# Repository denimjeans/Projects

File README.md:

Projekte
========

My self made electronic Projects.
Inclues all Files of the Project (Software and Hardware).

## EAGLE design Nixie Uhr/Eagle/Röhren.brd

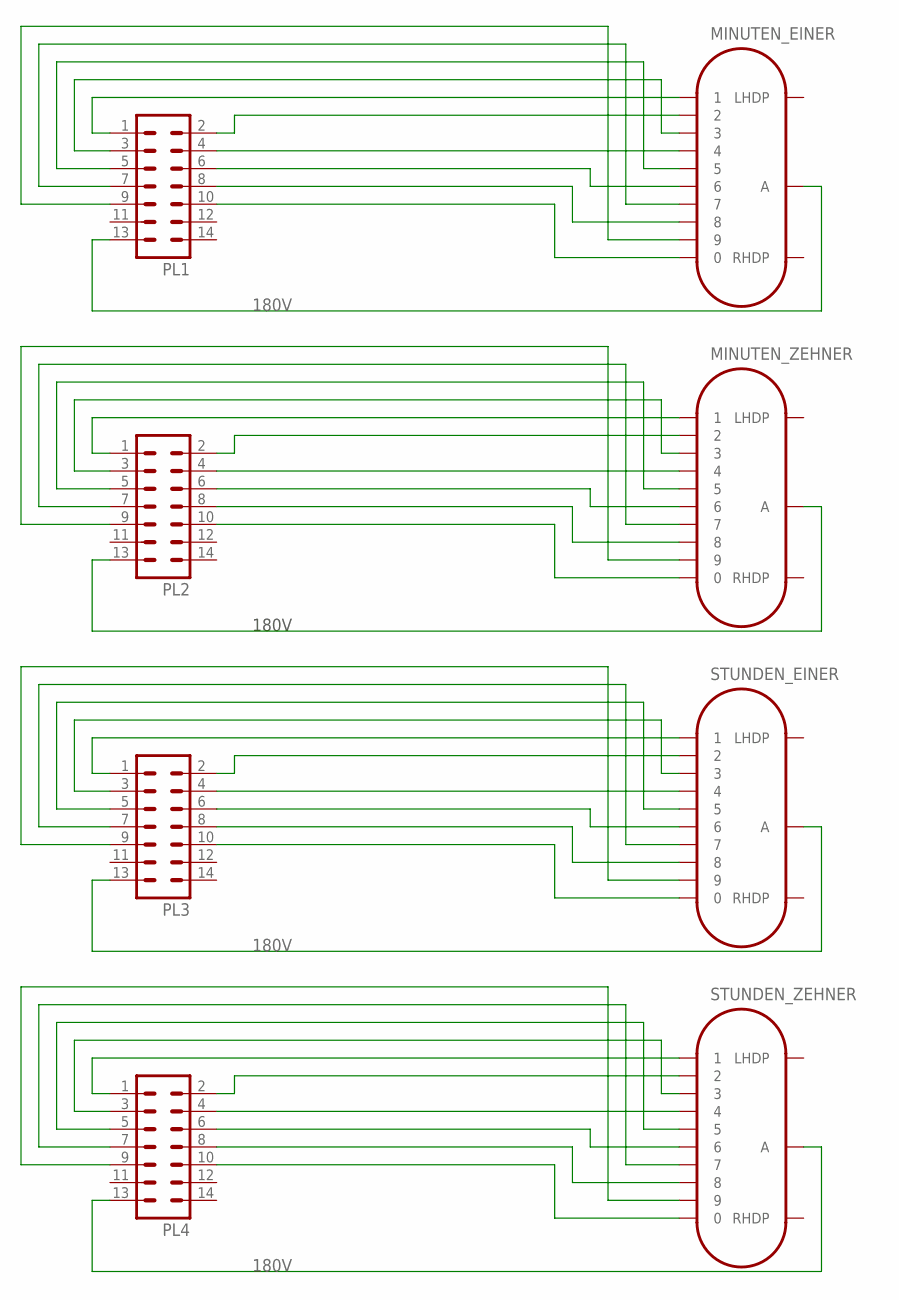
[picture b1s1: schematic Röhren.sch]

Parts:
MINUTEN_EINER: IN-16
MINUTEN_ZEHNER: IN-16
PL1, PL2, PL3, PL4: ML14
STUNDEN_EINER: IN-16
STUNDEN_ZEHNER: IN-16

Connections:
unnamed: MINUTEN_EINER.1, PL1.1
unnamed: MINUTEN_ZEHNER.1, PL2.1
unnamed: PL3.1, STUNDEN_EINER.1
unnamed: PL3.2, STUNDEN_EINER.2
unnamed: MINUTEN_EINER.2, PL1.2
unnamed: MINUTEN_EINER.3, PL1.3
unnamed: MINUTEN_EINER.4, PL1.4
unnamed: MINUTEN_EINER.5, PL1.5
unnamed: MINUTEN_EINER.6, PL1.6
unnamed: MINUTEN_EINER.8, PL1.8
unnamed: MINUTEN_EINER.9, PL1.9
unnamed: MINUTEN_EINER.0, PL1.10
unnamed: MINUTEN_EINER.A, PL1.13
unnamed: MINUTEN_ZEHNER.6, PL2.6
unnamed: MINUTEN_ZEHNER.2, PL2.2
unnamed: MINUTEN_ZEHNER.3, PL2.3
unnamed: MINUTEN_ZEHNER.4, PL2.4
unnamed: MINUTEN_ZEHNER.5, PL2.5
unnamed: MINUTEN_ZEHNER.7, PL2.7
unnamed: MINUTEN_ZEHNER.8, PL2.8
unnamed: MINUTEN_ZEHNER.9, PL2.9
unnamed: MINUTEN_ZEHNER.0, PL2.10
unnamed: MINUTEN_ZEHNER.A, PL2.13
unnamed: PL3.3, STUNDEN_EINER.3
unnamed: PL3.4, STUNDEN_EINER.4
unnamed: PL3.5, STUNDEN_EINER.5
unnamed: PL3.6, STUNDEN_EINER.6
unnamed: PL3.7, STUNDEN_EINER.7
unnamed: PL3.8, STUNDEN_EINER.8
unnamed: PL3.9, STUNDEN_EINER.9
unnamed: PL3.10, STUNDEN_EINER.0
unnamed: PL3.13, STUNDEN_EINER.A
unnamed: PL4.1, STUNDEN_ZEHNER.1
unnamed: PL4.2, STUNDEN_ZEHNER.2
unnamed: PL4.3, STUNDEN_ZEHNER.3
unnamed: PL4.4, STUNDEN_ZEHNER.4
unnamed: PL4.5, STUNDEN_ZEHNER.5
unnamed: PL4.6, STUNDEN_ZEHNER.6
unnamed: PL4.7, STUNDEN_ZEHNER.7
unnamed: PL4.8, STUNDEN_ZEHNER.8
unnamed: PL4.9, STUNDEN_ZEHNER.9
unnamed: PL4.10, STUNDEN_ZEHNER.0
unnamed: PL4.13, STUNDEN_ZEHNER.A
STUNDEN_ZEHNER: MINUTEN_EINER.7, PL1.7

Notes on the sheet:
180V

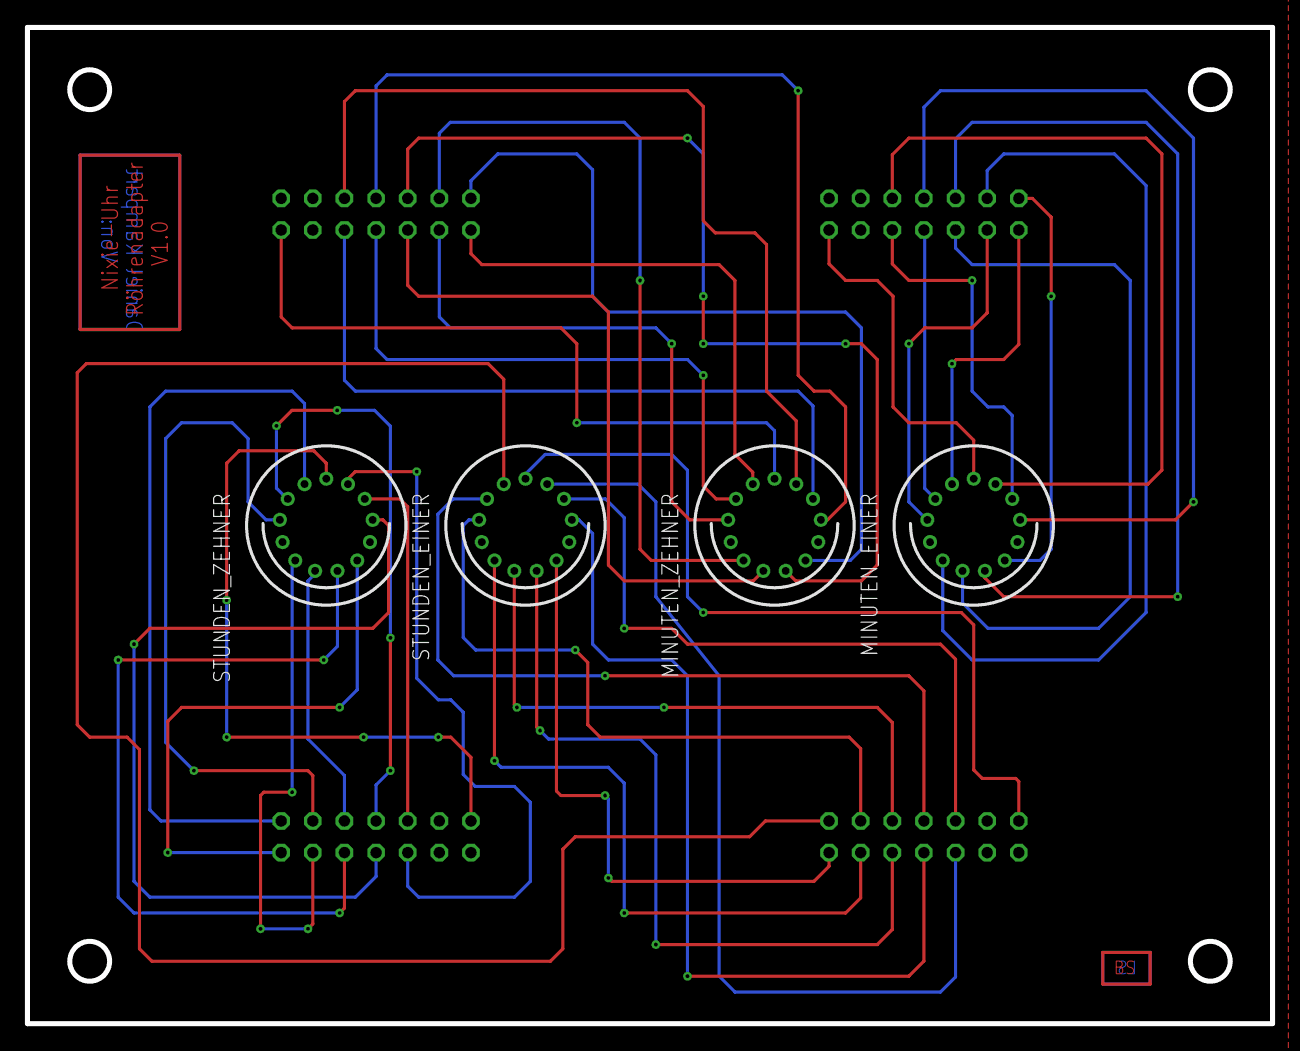
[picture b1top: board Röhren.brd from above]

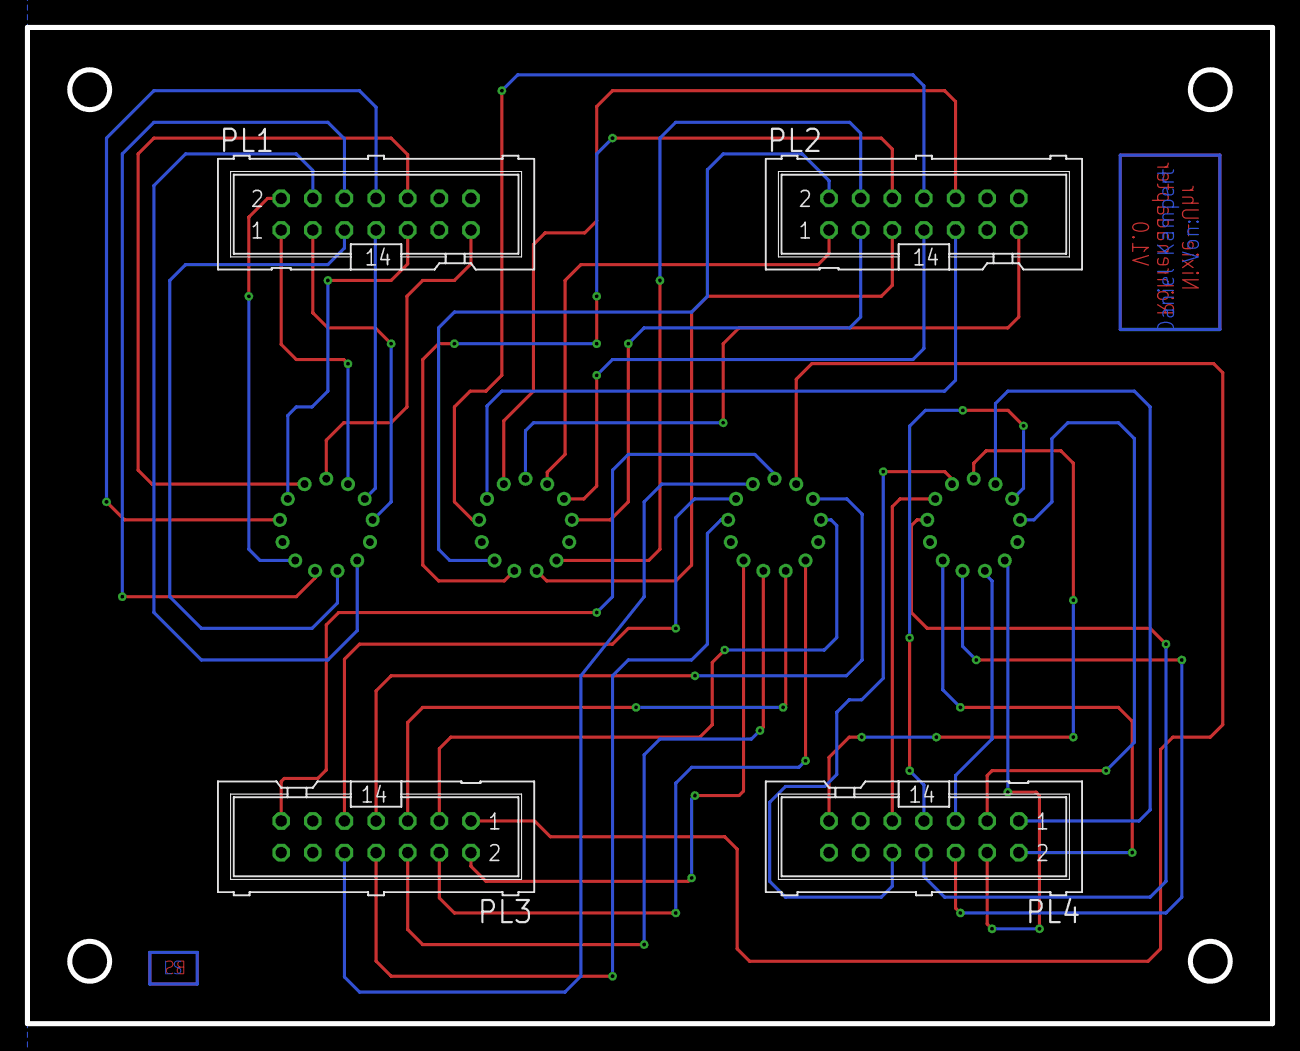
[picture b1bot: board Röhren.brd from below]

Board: 2 copper layers, 100.0 x 80.0 mm, 8 parts (4 on the bottom side), 44 nets.

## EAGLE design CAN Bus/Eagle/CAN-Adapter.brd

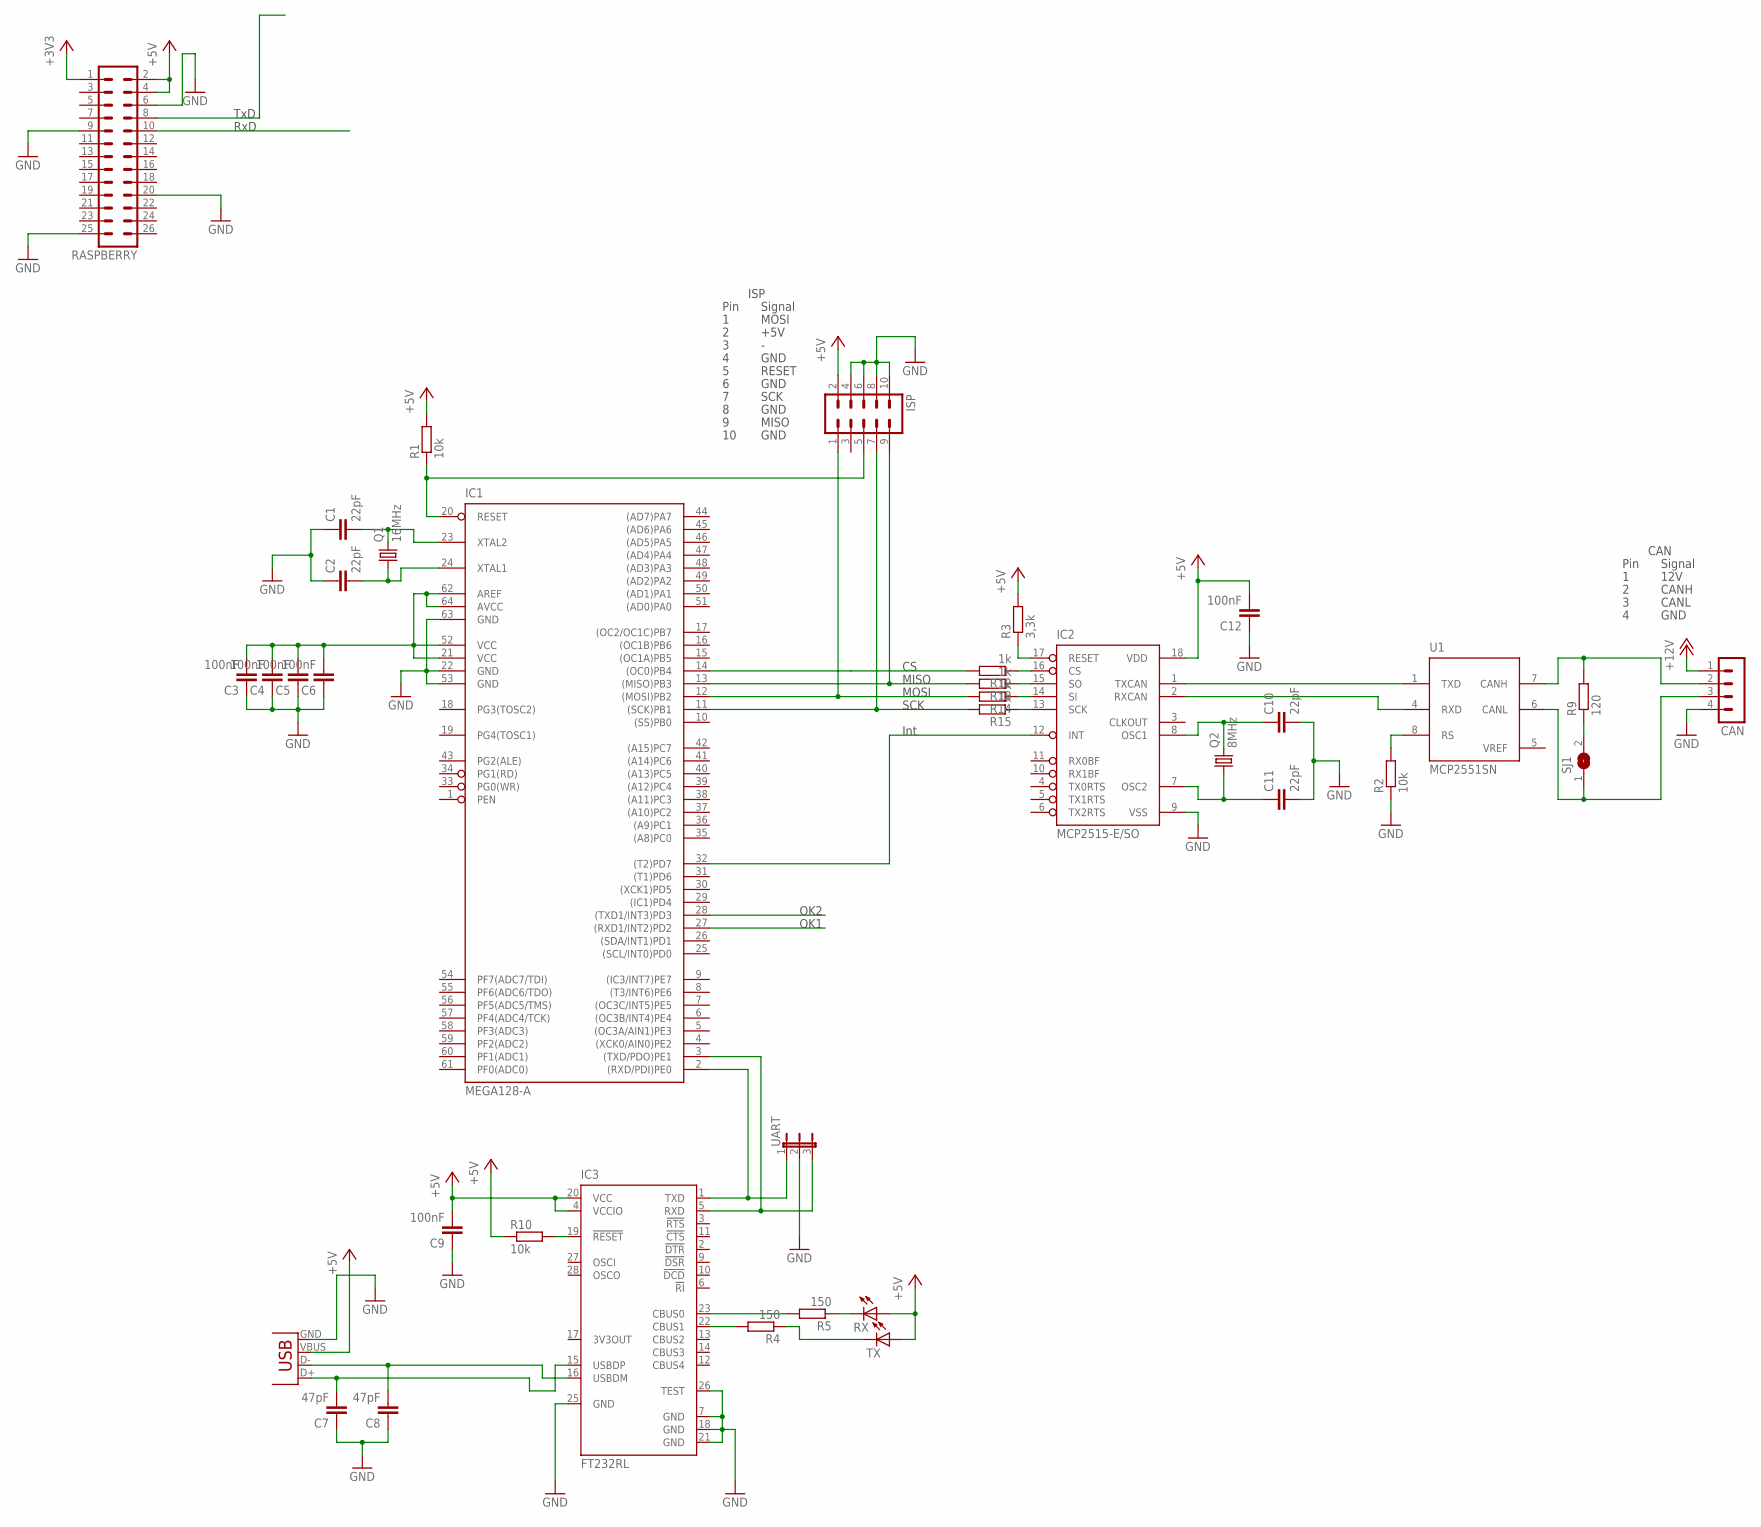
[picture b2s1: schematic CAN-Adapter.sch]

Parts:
C1, C2, C10, C11: 22pF; C0805
C3, C4, C5, C6, C9, C12: 100nF; C0805
C7, C8: 47pF; C0805
CAN: MA04-1
IC1: MEGA128-A; TQFP64
IC2: MCP2515-E/SO; SO18L
IC3: FT232RL; SSOP28
ISP: ML10
Q1: 16MHz; CSM-7X-DU
Q2: 8MHz; HC49UP
R1: 10k; R0805
R2, R10: 10k; M0805
R3: 3,3k; M0805
R4, R5: 150; M0805
R9: 120; M0805
R12, R13, R14, R15: 1k; R0402
RASPBERRY: MA13-2
RX: LEDCHIP-LED0805; CHIP-LED0805
SJ1: SJ
TX: LEDCHIP-LED0805; CHIP-LED0805
U1: MCP2551SN; SO-08
UART: JP2E; JP2
X1: USB-B-H

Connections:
+3V3: RASPBERRY.1
+5V: C9.2, C12.2, IC2.18 (VDD), IC3.4 (VCCIO), IC3.20 (VCC), ISP.2, R1.2, R3.2, R10.1, RASPBERRY.2, RASPBERRY.4, RX.A, TX.A, X1.VBUS
+12V: CAN.1
CANH: CAN.2, R9.2, U1.7 (CANH)
CANL: CAN.3, SJ1.1, U1.6 (CANL)
CHIPSELECT: IC1.14 ((OC0)PB4), R12.2
D+: C7.2, IC3.15 (USBDP), X1.D+
D-: C8.2, IC3.16 (USBDM), X1.D-
GND: C1.1, C2.1, C3.1, C4.1, C5.1, C6.1, C7.1, C8.1, C9.1, C10.2, C11.2, C12.1, CAN.4, IC1.22 (GND), IC1.53 (GND), IC1.63 (GND), IC2.9 (VSS), IC3.7 (GND), IC3.18 (GND), IC3.21 (GND), IC3.25 (GND), IC3.26 (TEST), ISP.4, ISP.6, ISP.8, ISP.10, R2.1, RASPBERRY.6, RASPBERRY.9, RASPBERRY.20, RASPBERRY.25, UART.2, X1.GND
MISO1: IC1.13 ((MISO)PB3), ISP.9, R13.2
MOSI: IC1.12 ((MOSI)PB2), ISP.1, R14.2
unnamed: C1.2, IC1.23 (XTAL2), Q1.2
unnamed: C2.2, IC1.24 (XTAL1), Q1.1
unnamed: R2.2, U1.8 (RS)
unnamed: IC1.20 (RESET), ISP.5, R1.1
unnamed: C3.2, C4.2, C5.2, C6.2, IC1.21 (VCC), IC1.52 (VCC), IC1.62 (AREF), IC1.64 (AVCC)
unnamed: IC2.2 (RXCAN), U1.4 (RXD)
unnamed: IC2.1 (TXCAN), U1.1 (TXD)
unnamed: IC3.23 (CBUS0), R5.2
unnamed: C11.1, IC2.7 (OSC2), Q2.1
unnamed: C10.1, IC2.8 (OSC1), Q2.2
unnamed: IC2.17 (RESET), R3.1
unnamed: R4.1, TX.C
unnamed: R5.1, RX.C
unnamed: IC3.22 (CBUS1), R4.2
unnamed: IC1.32 ((T2)PD7), IC2.12 (INT)
unnamed: IC3.19 (!RESET), R10.2
unnamed: R9.1, SJ1.2
unnamed: IC2.13 (SCK), R15.1
unnamed: IC2.14 (SI), R14.1
unnamed: IC2.15 (SO), R13.1
unnamed: IC2.16 (CS), R12.1
RX: IC1.2 ((RXD/PDI)PE0), IC3.1 (TXD), UART.1
RXD: RASPBERRY.10
RXD1: IC1.27 ((RXD1/INT2)PD2)
SCK1: IC1.11 ((SCK)PB1), ISP.7, R15.2
TX: IC1.3 ((TXD/PDO)PE1), IC3.5 (RXD), UART.3
TXD: RASPBERRY.8
TXD1: IC1.28 ((TXD1/INT3)PD3)
VDD: U1.3 (VDD)
VREF: U1.5 (VREF)
VSS: U1.2 (VSS)

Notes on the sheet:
Pin
Signal
MOSI
+5V
GND
ISP
RESET
SCK
MISO
Int
12V
CANH
CANL
CAN
TxD
RxD
OK1
OK2

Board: 2 copper layers, 37 parts (0 on the bottom side), 33 nets, no tracks yet.

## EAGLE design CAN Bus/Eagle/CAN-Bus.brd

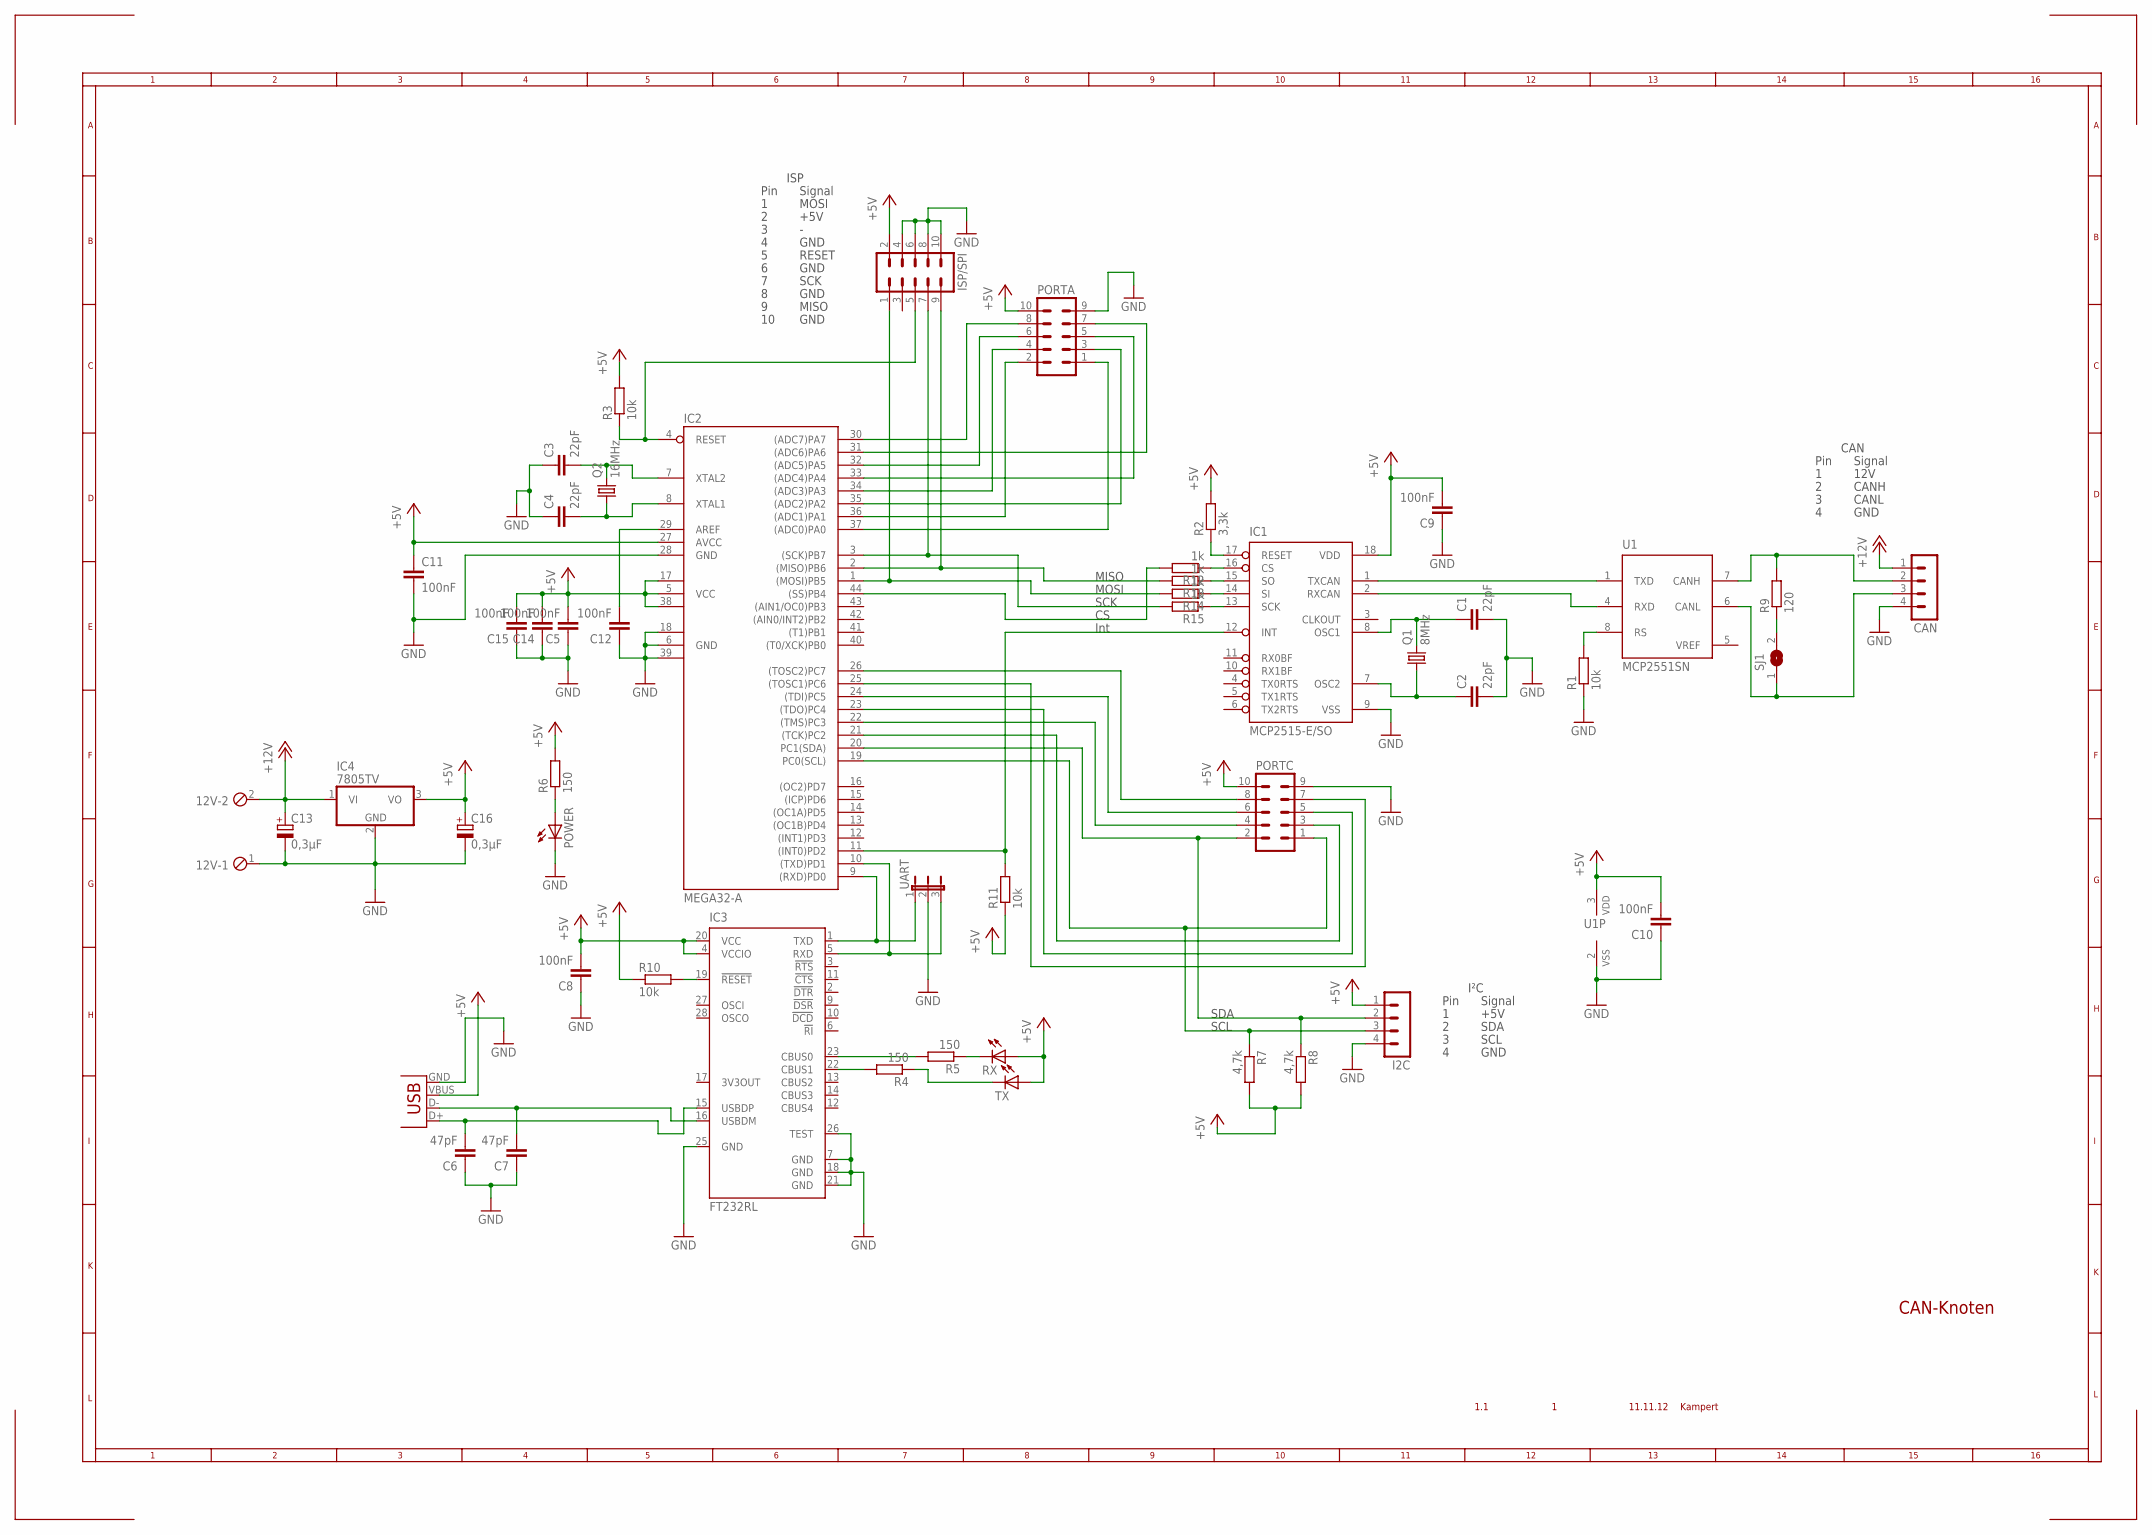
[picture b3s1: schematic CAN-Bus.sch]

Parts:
12V: MPT2; 2POL254
C1, C2, C3, C4: 22pF; C0805
C5, C8, C9, C10, C11, C12, C14, C15: 100nF; C0805
C6, C7: 47pF; C0805
C13, C16: 0,3µF; 153CLV-0405
CAN: MA04-1
I2C: MA04-1
IC1: MCP2515-E/SO; SO18L
IC2: MEGA32-A; TQFP44
IC3: FT232RL; SSOP28
IC4: 7805TV; TO220V
ISP/SPI: ML10
PORTA: ML10
PORTC: ML10
POWER: LEDCHIP-LED0805; CHIP-LED0805
Q1: 8MHz; HC49UP
Q2: 16MHz; HC49UP
R1, R3, R10, R11: 10k; M0805
R2: 3,3k; M0805
R4, R5, R6: 150; M0805
R7, R8: 4,7k; M0805
R9: 120; M0805
R12, R13, R14, R15: 1k; R0402
RX: LEDCHIP-LED0805; CHIP-LED0805
SJ1: SJ
TX: LEDCHIP-LED0805; CHIP-LED0805
U1: MCP2551SN; SO-08
UART: JP2E; JP2
X1: USB-B-H

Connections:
+5V: C5.2, C8.2, C9.2, C10.2, C11.1, C14.2, C15.2, C16.+, I2C.1, IC1.18 (VDD), IC2.5 (VCC), IC2.17 (VCC1), IC2.27 (AVCC), IC2.38 (VCC2), IC3.4 (VCCIO), IC3.20 (VCC), IC4.3 (VO), ISP/SPI.2, PORTA.10, PORTC.10, R2.2, R3.2, R6.2, R7.2, R8.2, R10.1, R11.1, RX.A, TX.A, U1.3 (VDD), X1.VBUS
+12V: 12V.2, C13.+, CAN.1, IC4.1 (VI)
CANH: CAN.2, R9.2, U1.7 (CANH)
CANL: CAN.3, SJ1.1, U1.6 (CANL)
CHIPSELECT: IC2.44 ((SS)PB4), R12.2
D+: C6.2, IC3.15 (USBDP), X1.D+
D-: C7.2, IC3.16 (USBDM), X1.D-
GND: 12V.1, C1.2, C2.2, C3.1, C4.1, C5.1, C6.1, C7.1, C8.1, C9.1, C10.1, C11.2, C12.1, C13.-, C14.1, C15.1, C16.-, CAN.4, I2C.4, IC1.9 (VSS), IC2.6 (GND), IC2.18 (GND1), IC2.28 (GND), IC2.39 (GND2), IC3.7 (GND), IC3.18 (GND), IC3.21 (GND), IC3.25 (GND), IC3.26 (TEST), IC4.2 (GND), ISP/SPI.4, ISP/SPI.6, ISP/SPI.8, ISP/SPI.10, PORTA.9, PORTC.9, POWER.C, R1.1, U1.2 (VSS), UART.2, X1.GND
MISO: IC2.2 ((MISO)PB6), ISP/SPI.9, R13.2
MOSI: IC2.1 ((MOSI)PB5), ISP/SPI.1, R14.2
unnamed: C4.2, IC2.8 (XTAL1), Q2.1
unnamed: R1.2, U1.8 (RS)
unnamed: C3.2, IC2.7 (XTAL2), Q2.2
unnamed: IC3.23 (CBUS0), R5.2
unnamed: IC1.1 (TXCAN), U1.1 (TXD)
unnamed: IC1.2 (RXCAN), U1.4 (RXD)
unnamed: C2.1, IC1.7 (OSC2), Q1.1
unnamed: C1.1, IC1.8 (OSC1), Q1.2
unnamed: IC1.17 (RESET), R2.1
unnamed: R4.1, TX.C
unnamed: R5.1, RX.C
unnamed: IC3.22 (CBUS1), R4.2
unnamed: IC2.37 ((ADC0)PA0), PORTA.1
unnamed: IC2.36 ((ADC1)PA1), PORTA.2
unnamed: IC2.35 ((ADC2)PA2), PORTA.3
unnamed: IC2.34 ((ADC3)PA3), PORTA.4
unnamed: IC2.33 ((ADC4)PA4), PORTA.5
unnamed: IC2.32 ((ADC5)PA5), PORTA.6
unnamed: IC2.31 ((ADC6)PA6), PORTA.7
unnamed: IC2.30 ((ADC7)PA7), PORTA.8
unnamed: IC1.12 (INT), IC2.11 ((INT0)PD2), R11.2
unnamed: IC2.21 ((TCK)PC2), PORTC.3
unnamed: IC2.22 ((TMS)PC3), PORTC.4
unnamed: IC2.23 ((TDO)PC4), PORTC.5
unnamed: IC2.24 ((TDI)PC5), PORTC.6
unnamed: IC2.25 ((TOSC1)PC6), PORTC.7
unnamed: IC2.26 ((TOSC2)PC7), PORTC.8
unnamed: POWER.A, R6.1
unnamed: IC3.19 (!RESET), R10.2
unnamed: C12.2, IC2.29 (AREF)
unnamed: R9.1, SJ1.2
unnamed: IC1.13 (SCK), R15.1
unnamed: IC1.14 (SI), R14.1
unnamed: IC1.15 (SO), R13.1
unnamed: IC1.16 (CS), R12.1
RESET: IC2.4 (RESET), ISP/SPI.5, R3.1
RX: IC2.9 ((RXD)PD0), IC3.1 (TXD), UART.1
SCK: IC2.3 ((SCK)PB7), ISP/SPI.7, R15.2
SCL: I2C.3, IC2.19 (PC0(SCL)), PORTC.1, R7.1
SDA: I2C.2, IC2.20 (PC1(SDA)), PORTC.2, R8.1
TX: IC2.10 ((TXD)PD1), IC3.5 (RXD), UART.3
VREF: U1.5 (VREF)

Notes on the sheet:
SCK
MOSI
MISO
Int
SDA
SCL
Pin
Signal
12V
CANH
CANL
GND
CAN
+5V
I²C
ISP
RESET
1.1
11.11.12
Kampert
CAN-Knoten

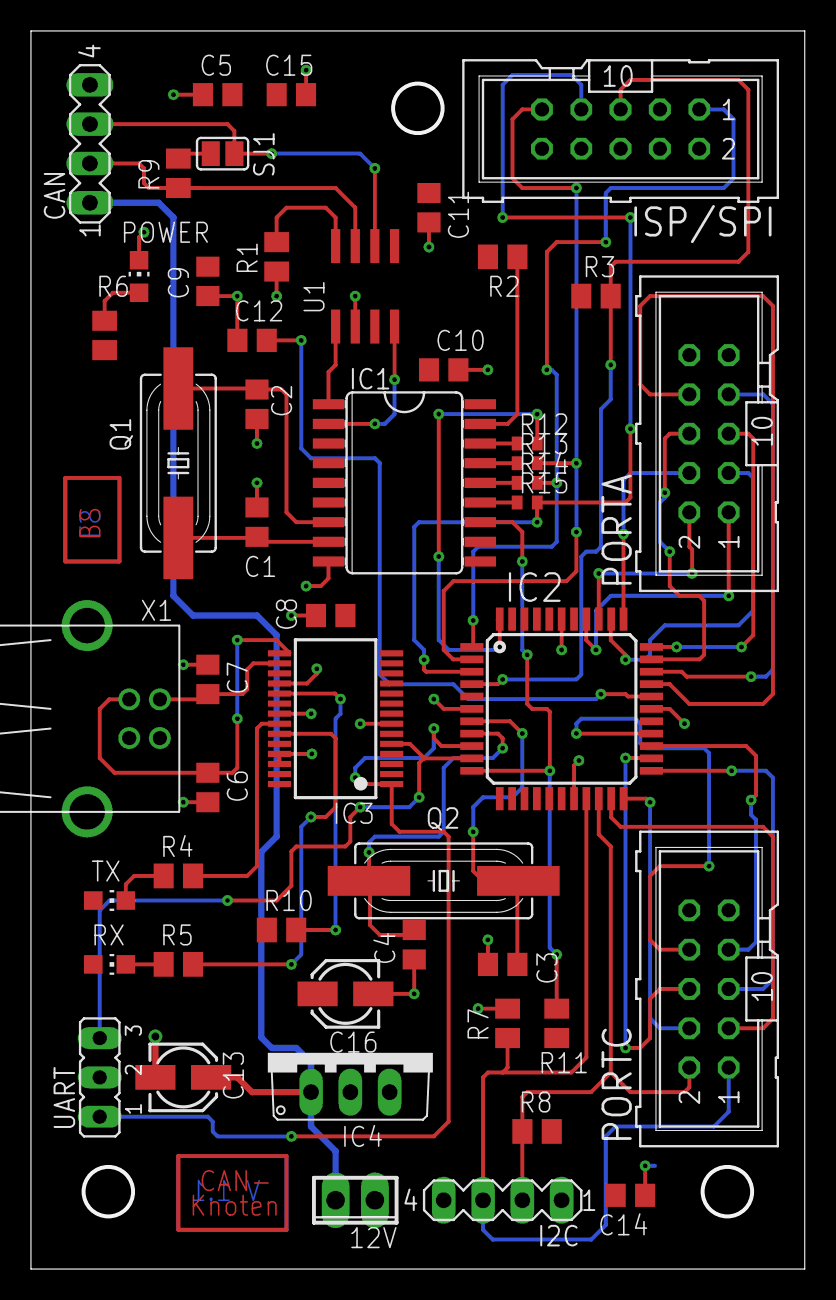
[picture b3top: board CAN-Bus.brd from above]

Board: 2 copper layers, 49.7 x 79.7 mm, 50 parts (0 on the bottom side), 51 nets.

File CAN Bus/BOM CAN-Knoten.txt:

Bauteil Wert         Device             Package      Description                                                            
12V                  MPT2               2POL254      PHOENIX CONNECTOR                                                      
C1      22pF         C-EUC0805          C0805        CAPACITOR, European symbol                                             
C2      22pF         C-EUC0805          C0805        CAPACITOR, European symbol                                             
C3      22pF         C-EUC0805          C0805        CAPACITOR, European symbol                                             
C4      22pF         C-EUC0805          C0805        CAPACITOR, European symbol                                             
C5      100nF        C-EUC0805          C0805        CAPACITOR, European symbol                                             
C6      47pF         C-EUC0805          C0805        CAPACITOR, European symbol                                             
C7      47pF         C-EUC0805          C0805        CAPACITOR, European symbol                                             
C8      100nF        C-EUC0805          C0805        CAPACITOR, European symbol                                             
C9      100nF        C-EUC0805          C0805        CAPACITOR, European symbol                                             
C10     100nF        C-EUC0805          C0805        CAPACITOR, European symbol                                             
C11     100nF        C-EUC0805          C0805        CAPACITOR, European symbol                                             
C12     100nF        C-EUC0805          C0805        CAPACITOR, European symbol                                             
C13     0,3µF        CPOL-EU153CLV-0405 153CLV-0405  POLARIZED CAPACITOR, European symbol                                   
C14     100nF        C-EUC0805          C0805        CAPACITOR, European symbol                                             
C15     100nF        C-EUC0805          C0805        CAPACITOR, European symbol                                             
C16     0,3µF        CPOL-EU153CLV-0405 153CLV-0405  POLARIZED CAPACITOR, European symbol                                   
CAN                  MA04-1             MA04-1       PIN HEADER                                                             
I2C                  MA04-1             MA04-1       PIN HEADER                                                             
IC1     MCP2515-E/SO MCP2515-E/SO       SO18L                                                                               
IC2     MEGA32-A     MEGA32-A           TQFP44       MICROCONTROLLER                                                        
IC3     FT232RL      FT232RL            SSOP28       Source: http://www.ftdichip.com/Documents/DataSheets/DS_FT232R_v104.pdf
IC4     7805TV       7805TV             TO220V       Positive VOLTAGE REGULATOR                                             
ISP/SPI              ML10               ML10         HARTING                                                                
PORTA                ML10               ML10         HARTING                                                                
PORTC                ML10               ML10         HARTING                                                                
POWER                LEDCHIP-LED0805    CHIP-LED0805 LED                                                                    
Q1      8MHz         CRYSTALHC49UP      HC49UP       CRYSTAL                                                                
Q2      16MHz        CRYSTALHC49UP      HC49UP       CRYSTAL                                                                
R1      10k          R-EU_M0805         M0805        RESISTOR, European symbol                                              
R2      3,3k         R-EU_M0805         M0805        RESISTOR, European symbol                                              
R3      10k          R-EU_M0805         M0805        RESISTOR, European symbol                                              
R4      150          R-EU_M0805         M0805        RESISTOR, European symbol                                              
R5      150          R-EU_M0805         M0805        RESISTOR, European symbol                                              
R6      150          R-EU_M0805         M0805        RESISTOR, European symbol                                              
R7      4,7k         R-EU_M0805         M0805        RESISTOR, European symbol                                              
R8      4,7k         R-EU_M0805         M0805        RESISTOR, European symbol                                              
R9      120          R-EU_M0805         M0805        RESISTOR, European symbol                                              
R10     10k          R-EU_M0805         M0805        RESISTOR, European symbol                                              
R11     10k          R-EU_M0805         M0805        RESISTOR, European symbol                                              
R12     1k           R-EU_R0402         R0402        RESISTOR, European symbol                                              
R13     1k           R-EU_R0402         R0402        RESISTOR, European symbol                                              
R14     1k           R-EU_R0402         R0402        RESISTOR, European symbol                                              
R15     1k           R-EU_R0402         R0402        RESISTOR, European symbol                                              
RX                   LEDCHIP-LED0805    CHIP-LED0805 LED                                                                    
SJ1                  SJ                 SJ           SMD solder JUMPER                                                      
TX                   LEDCHIP-LED0805    CHIP-LED0805 LED                                                                    
U1      MCP2551SN    MCP2551SN          SO-08        High Speed CAN tranceiver                                              
UART                 JP2E               JP2          JUMPER                                                                 
X1      USB-B-H      USB-B-H            USB-B-H      USB Connectors
